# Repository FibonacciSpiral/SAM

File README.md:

# SAM: Single Channel Temperature Monitor  

## Overview

**SAM** (Single-channel Analog Monitor) is a low-cost temperature monitor designed to enable simple temperature monitoring on a variety of TMS heaters. It continuously measures temperature using a Type K thermocouple and alerts operators when the temperature drops below a configured setpoint. The goal is to provide an inexpensive, accurate, and user-friendly thermal monitoring system suitable for industrial or laboratory environments.

## Features
- **Single-channel thermocouple monitoring** via MAX31855K  
- **Configurable setpoint** through a simple 3-button interface (Up, Down, Set)  
- **Real-time temperature display** on a 3-digit seven-segment display  
- **Alert relay output** (N.O. relay circuit) to notify external systems of low-temperature conditions  
- **Modbus TCP/IP server** for remote data retrieval  
- **Web and FTP interfaces** for configuration and resource management  
- **Persistent settings** stored in eMMC non-volatile memory  
- **FreeRTOS-based firmware** using Microchip Studio and ASF (Atmel Software Framework)  

## Hardware Architecture
### Microcontroller
- **MCU Family:** ATSAM4S (ARM Cortex-M4, 120 MHz)  
- **Development Kit:** ATSAM4S Xplained Pro  
- **Networking:** KSZ8851SNL Ethernet controller via SPI  
- **Persistent Storage:** eMMC module (or SD card for prototyping)  

### Sensor Interface
- **Thermocouple Interface Chip:** MAX31855K  
- Provides cold-junction compensation and interfaces with MCU using SPI.

### Display & Input
- **Display:** Three 7-segment LED modules showing real-time temperature or setpoint during configuration.  
- **Buttons:**  
  - **Set:** Enter/exit configuration mode.  
  - **Up/Down:** Adjust setpoint during configuration.  
- **User Feedback:** Flashing display while adjusting setpoint.  

### Relay Output
- **Type:** Normally Open (N.O.) relay  
- **Behavior:**  
  - **High signal:** Normal operation  
  - **Low signal:** Setpoint violation or sensor/power fault  

## Software Architecture
### Operating System
- **RTOS:** FreeRTOS  
- **Language:** C  
- **IDE:** Microchip Studio (Atmel Studio)  

### Modules
#### 1. Temperature Reading
- SPI-based data acquisition from MAX31855K every millisecond for 2 seconds.  
- Average of readings computed for noise reduction.  
- Filtered temperature sent to display, setpoint, and relay tasks.  

#### 2. TCP/IP Stack & Networking
- Based on FreeRTOS+TCP.  
- Includes Ethernet MAC/PHY driver for KSZ8851SNL.  
- Network settings configurable via embedded web server.  

#### 3. Web & FTP Server
- Web interface for IP configuration and device setup.  
- FTP server for uploading web resources (HTML, JS, CSS) stored in eMMC.  

#### 4. Modbus Server
- Implements **Modbus TCP** using the FreeModbus library.  
- Stores current temperature in input register (prototype uses register `1000`).  
- Allows master devices to read temperature remotely.  

#### 5. User Interface Tasks
- **Button Handler:** Interrupt-driven; sends events to state machine task.  
- **Display Driver:** Updates 7-segment display according to operating mode.  
- **Setpoint Task:** Handles setpoint logic, relay control, and NVM storage.  

#### 6. Non-Volatile Memory
- Stores:  
  - Last known setpoint  
  - Network configuration  
  - Web/FTP server resources  
- Implemented with eMMC interface.  

## Development Environment
- **Hardware:** ATSAM4S Xplained Pro + Ethernet1 Xplained Pro extension board  
- **Software:**  
  - Microchip Studio (formerly Atmel Studio)  
  - FreeRTOS  
  - ASF (Atmel Software Framework)  
  - FreeModbus library  

## Prototyping Notes
- SD card may be used as a temporary stand-in for eMMC.  
- Ensure MAX31855K wiring minimizes stray capacitance for accuracy.  
- Software debouncing implemented for all buttons (no hardware debouncing required).  
- Recommended MCU RAM: **≥128kB** (prototype uses 160kB).   

## License
This project is not licensed for redistribution or modification.  
All rights reserved © 2025 Giselle Dockterburke.

## Authors
Software Developed by Giselle Dockterburke at the Hillsboro PC in collaboration with Div Tummala who designed the hardware configuration.

---

**Revision History:**  
See the full svn revision history in the documentation folder.

---

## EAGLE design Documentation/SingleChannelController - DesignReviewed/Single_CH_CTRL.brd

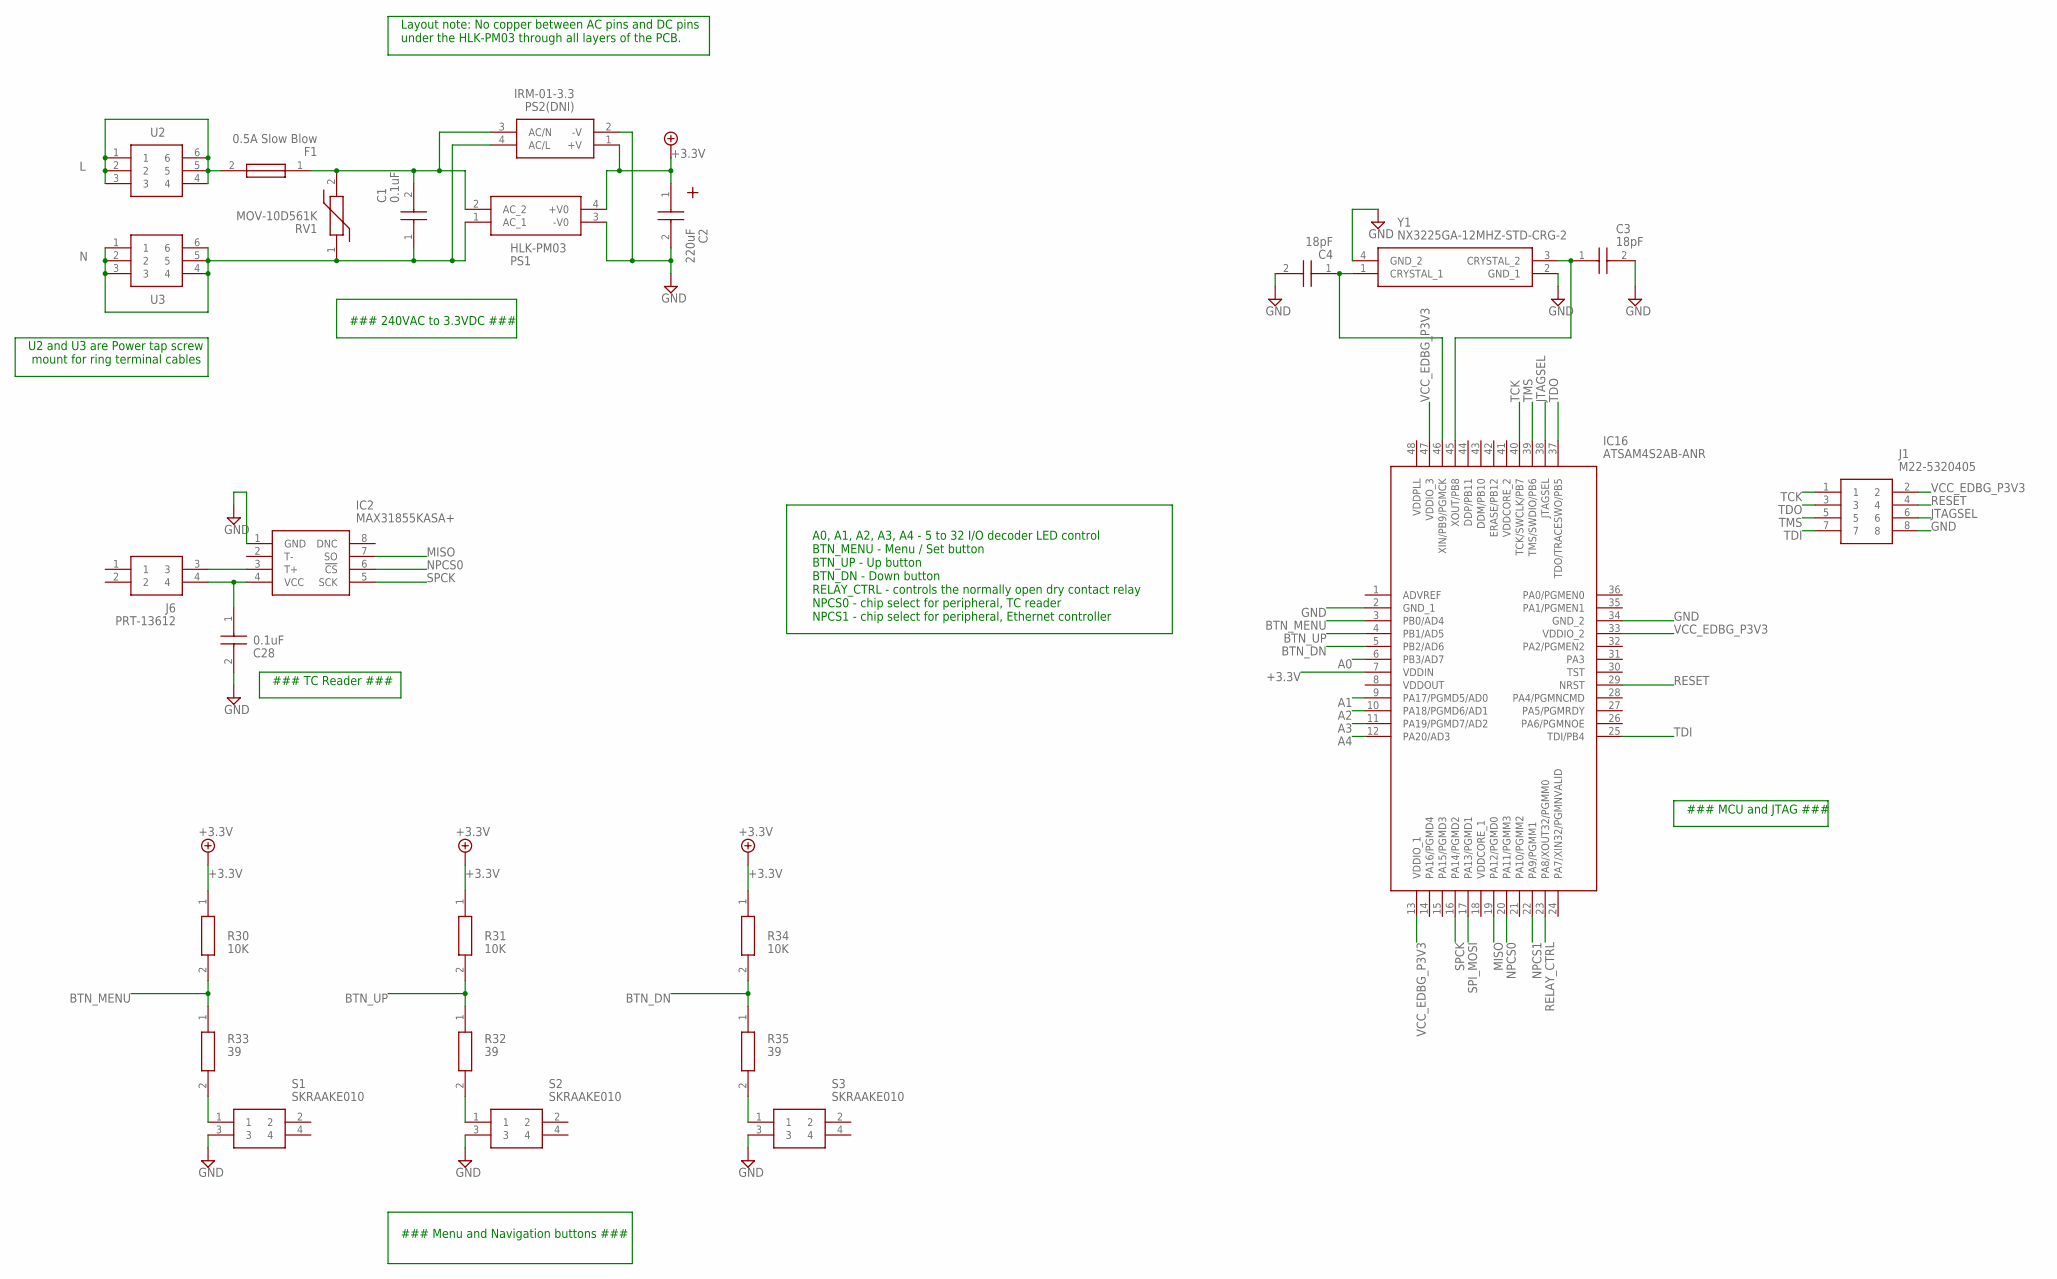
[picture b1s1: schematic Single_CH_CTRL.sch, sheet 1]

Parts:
C1: 0.1uF; B32922X_(18_X_5)
C2: 220uF; CAPPRD250W52D630H1250
C3, C4: 18pF; CAPC1005X56N
C28: 0.1uF; CAPC2012X88N
F1: 0.5A Slow Blow; RST500AMMO
IC2: MAX31855KASA+; SOIC127P600X175-8N
IC16: ATSAM4S2AB-ANR; QFP50P900X900X160-48N
J1: M22-5320405; HUSSP8W50P200_2X4_800X400X500P
J6: PRT-13612; PRT13612
PS1: HLK-PM03; HLKPM03
PS2(DNI): IRM-01-3.3; IRM015
R30, R31, R34: 10K; RESC1005X35N
R32, R33, R35: 39; RESC1005X40N
RV1: MOV-10D561K; MOV10D561K
S1, S2, S3: SKRAAKE010; SKRAAKE010_1
U2, U3: 5055323-9; 50553239
Y1: NX3225GA-12MHZ-STD-CRG-2; NX3225GA12MHZSTDCRG2

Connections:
+3.3V: C2.1 (+), IC16.7 (VDDIN), PS1.4 (+V0), PS2(DNI).1 (+V), R30.1, R31.1, R34.1; also elsewhere on the board
A0: IC16.6 (PB3/AD7)
A1: IC16.9 (PA17/PGMD5/AD0)
A2: IC16.10 (PA18/PGMD6/AD1)
A3: IC16.11 (PA19/PGMD7/AD2)
A4: IC16.12 (PA20/AD3)
BTN_DN: IC16.5 (PB2/AD6), R34.2, R35.1
BTN_MENU: IC16.3 (PB0/AD4), R30.2, R33.1
BTN_UP: IC16.4 (PB1/AD5), R31.2, R32.1
GND: C2.2 (-), C3.2, C4.2, C28.2, IC2.1 (GND), IC16.2 (GND_1), IC16.34 (GND_2), J1.8, PS1.3 (-V0), PS2(DNI).2 (-V), S1.3, S2.3, S3.3, Y1.2 (GND_1), Y1.4 (GND_2); also elsewhere on the board
JTAGSEL: IC16.38 (JTAGSEL), J1.6
L: F1.2, U2.1, U2.2, U2.3, U2.4, U2.5, U2.6
MISO: IC2.7 (SO), IC16.19 (PA12/PGMD0); also elsewhere on the board
N: C1.1, PS1.1 (AC_1), PS2(DNI).4 (AC/L), RV1.1, U3.1, U3.2, U3.3, U3.4, U3.5, U3.6
unnamed: C1.2, F1.1, PS1.2 (AC_2), PS2(DNI).3 (AC/N), RV1.2
unnamed: C3.1, IC16.45 (XOUT/PB8), Y1.3 (CRYSTAL_2)
unnamed: C4.1, IC16.46 (XIN/PB9/PGMCK), Y1.1 (CRYSTAL_1)
unnamed: R33.2, S1.1
unnamed: R32.2, S2.1
unnamed: R35.2, S3.1
unnamed: C28.1, IC2.4 (VCC), J6.4
unnamed: IC2.3 (T+), J6.3
NPCS0: IC2.6 (!CS), IC16.20 (PA11/PGMM3)
NPCS1: IC16.22 (PA9/PGMM1); also elsewhere on the board
RELAY_CTRL: IC16.23 (PA8/XOUT32/PGMM0); also elsewhere on the board
RESET: IC16.29 (NRST), J1.4
SPCK: IC2.5 (SCK), IC16.16 (PA14/PGMD2); also elsewhere on the board
SPI_MOSI: IC16.17 (PA13/PGMD1); also elsewhere on the board
TCK: IC16.40 (TCK/SWCLK/PB7), J1.1
TDI: IC16.25 (TDI/PB4), J1.7
TDO: IC16.37 (TDO/TRACESWO/PB5), J1.3
TMS: IC16.39 (TMS/SWDIO/PB6), J1.5
VCC_EDBG_P3V3: IC16.13 (VDDIO_1), IC16.33 (VDDIO_2), IC16.47 (VDDIO_3), J1.2

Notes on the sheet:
A0, A1, A2, A3, A4 - 5 to 32 I/O decoder LED control BTN_MENU - Menu / Set button BTN_UP - Up button BTN_DN - Down button RELAY_CTRL - controls the normally open dry contact relay NPCS0 - chip select for peripheral, TC reader NPCS1 - chip select for peripheral, Ethernet controller
Layout note: No copper between AC pins and DC pins under the HLK-PM03 through all layers of the PCB.
### 240VAC to 3.3VDC ###
### TC Reader ###
### MCU and JTAG ###
### Menu and Navigation buttons ###
U2 and U3 are Power tap screw mount for ring terminal cables

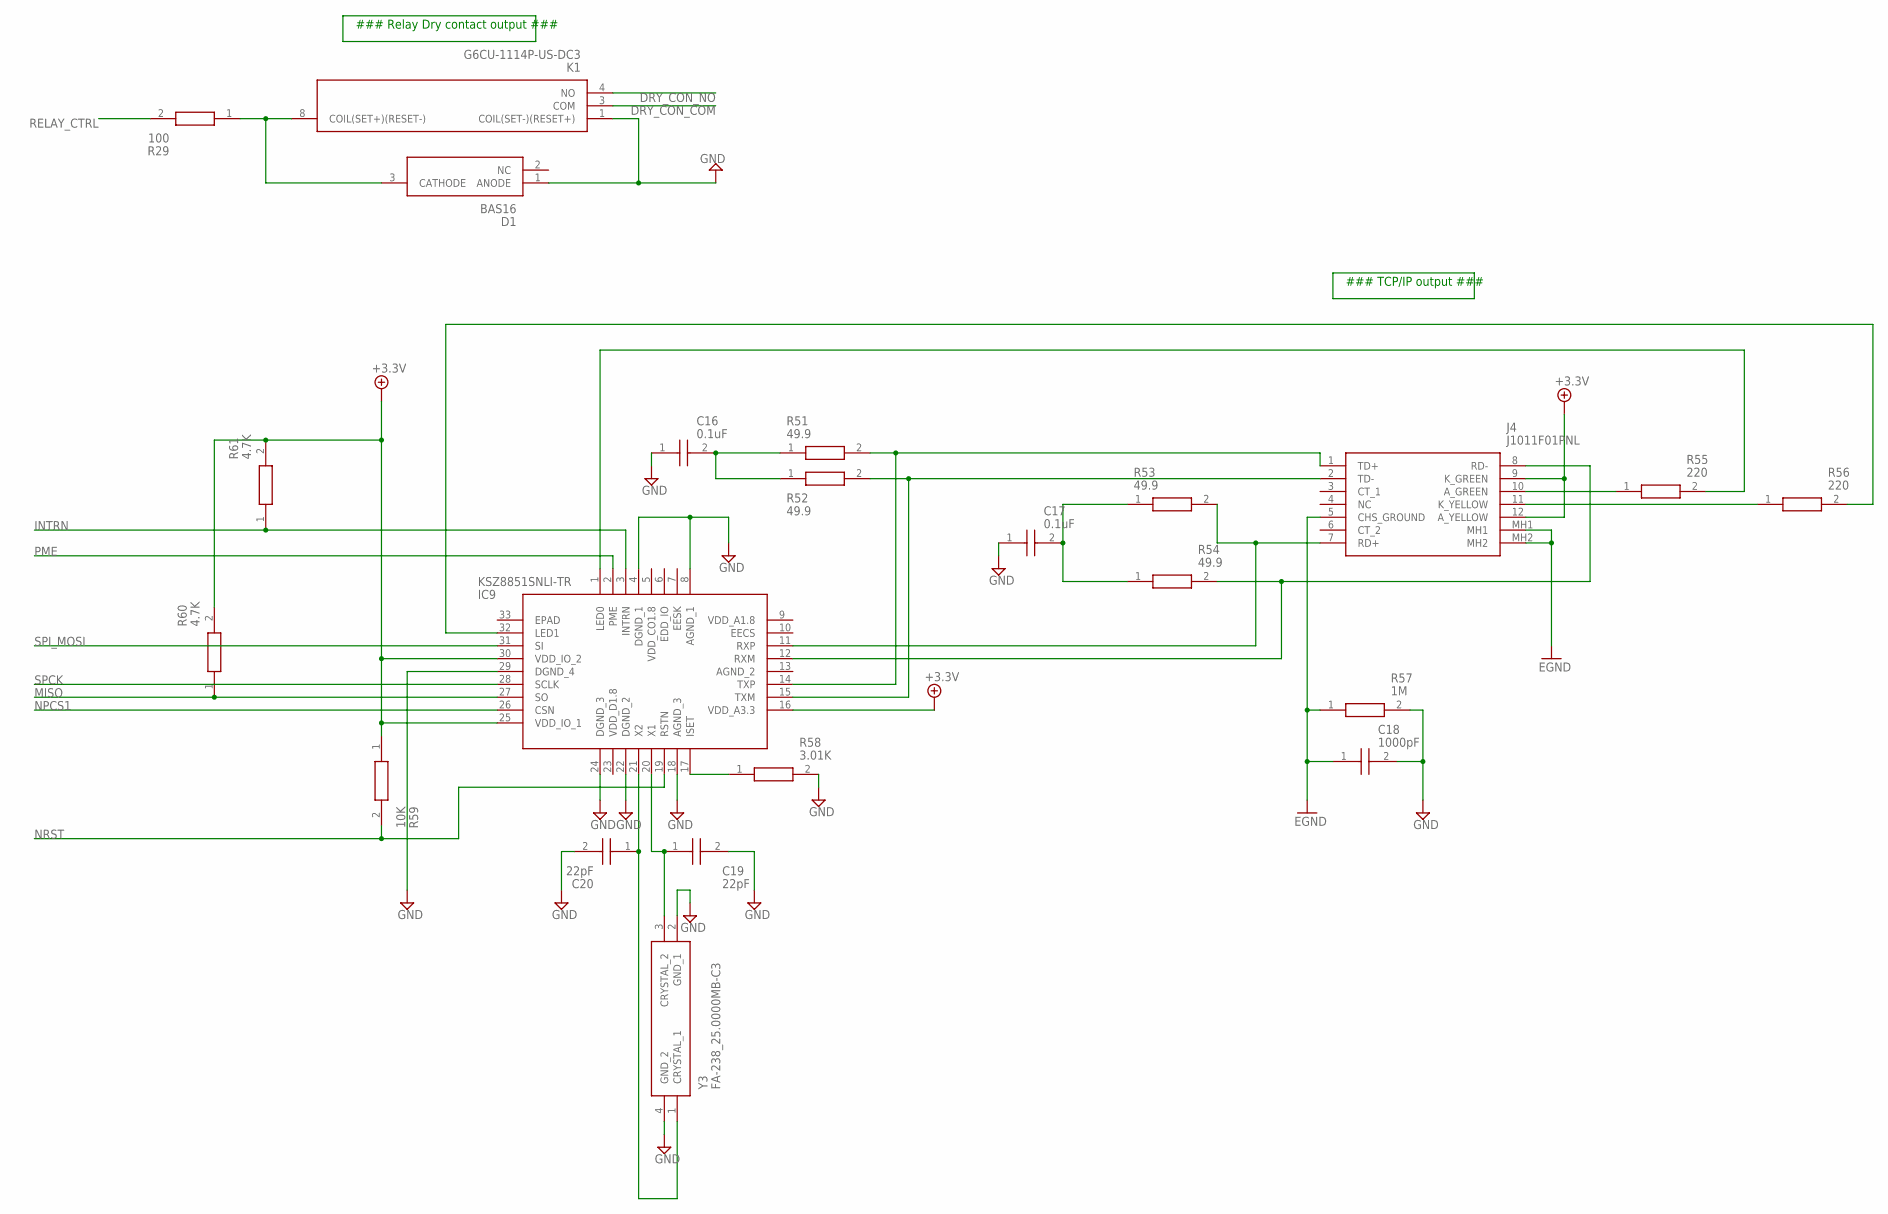
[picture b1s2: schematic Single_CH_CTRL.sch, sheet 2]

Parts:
C16, C17: 0.1uF; C0402
C18: 1000pF; C4520_COMMERCIAL
C19, C20: 22pF; CBR04C
D1: BAS16; SOT95P240X110-3N
IC9: KSZ8851SNLI-TR; QFN50P500X500X100-33N
J4: J1011F01PNL
K1: G6CU-1114P-US-DC3; G6CU1114PUSDC3
R29: 100; ERJP03_PA3_(0603)
R51, R52, R53, R54: 49.9; ERJS02_U02_(0402)
R55, R56: 220; RESC1005X40N
R57: 1M; RESC2012X60N
R58: 3.01K; RESC1005X40N
R59: 10K; RESC1005X40N
R60, R61: 4.7K; RESC1005X40N
Y3: FA-238_25.0000MB-C3; FA238300000MBC0

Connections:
+3.3V: IC9.16 (VDD_A3.3), IC9.25 (VDD_IO_1), IC9.30 (VDD_IO_2), J4.9 (K_GREEN), J4.12 (A_YELLOW), R59.1, R60.2, R61.2; also elsewhere on the board
DRY_CON_COM: K1.3 (COM)
DRY_CON_NO: K1.4 (NO)
GND: C16.1, C17.1, C18.1, C18.2, C19.2, C20.2, D1.1 (ANODE), IC9.4 (DGND_1), IC9.8 (AGND_1), IC9.18 (AGND_3), IC9.22 (DGND_2), IC9.24 (DGND_3), IC9.29 (DGND_4), J4.5 (CHS_GROUND), J4.MH1, J4.MH2, K1.1 (COIL(SET-)(RESET+)), R57.1, R57.2, R58.2, Y3.2 (GND_1), Y3.4 (GND_2); also elsewhere on the board
INTRN: IC9.3 (INTRN), R61.1
MISO: IC9.27 (SO), R60.1; also elsewhere on the board
unnamed: D1.3 (CATHODE), K1.8 (COIL(SET+)(RESET-)), R29.1
unnamed: IC9.14 (TXP), J4.1 (TD+), R51.2
unnamed: IC9.15 (TXM), J4.2 (TD-), R52.2
unnamed: IC9.11 (RXP), J4.7 (RD+), R53.2
unnamed: C16.2, R51.1, R52.1
unnamed: C17.2, R53.1, R54.1
unnamed: IC9.12 (RXM), J4.8 (RD-), R54.2
unnamed: J4.10 (A_GREEN), R55.1
unnamed: J4.11 (K_YELLOW), R56.1
unnamed: IC9.1 (LED0), R55.2
unnamed: IC9.32 (LED1), R56.2
unnamed: C19.1, IC9.20 (X1), Y3.3 (CRYSTAL_2)
unnamed: C20.1, IC9.21 (X2), Y3.1 (CRYSTAL_1)
unnamed: IC9.17 (ISET), R58.1
NPCS1: IC9.26 (CSN); also elsewhere on the board
NRST: IC9.19 (RSTN), R59.2
PME: IC9.2 (PME)
RELAY_CTRL: R29.2; also elsewhere on the board
SPCK: IC9.28 (SCLK); also elsewhere on the board
SPI_MOSI: IC9.31 (SI); also elsewhere on the board

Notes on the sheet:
### Relay Dry contact output ###
### TCP/IP output ###

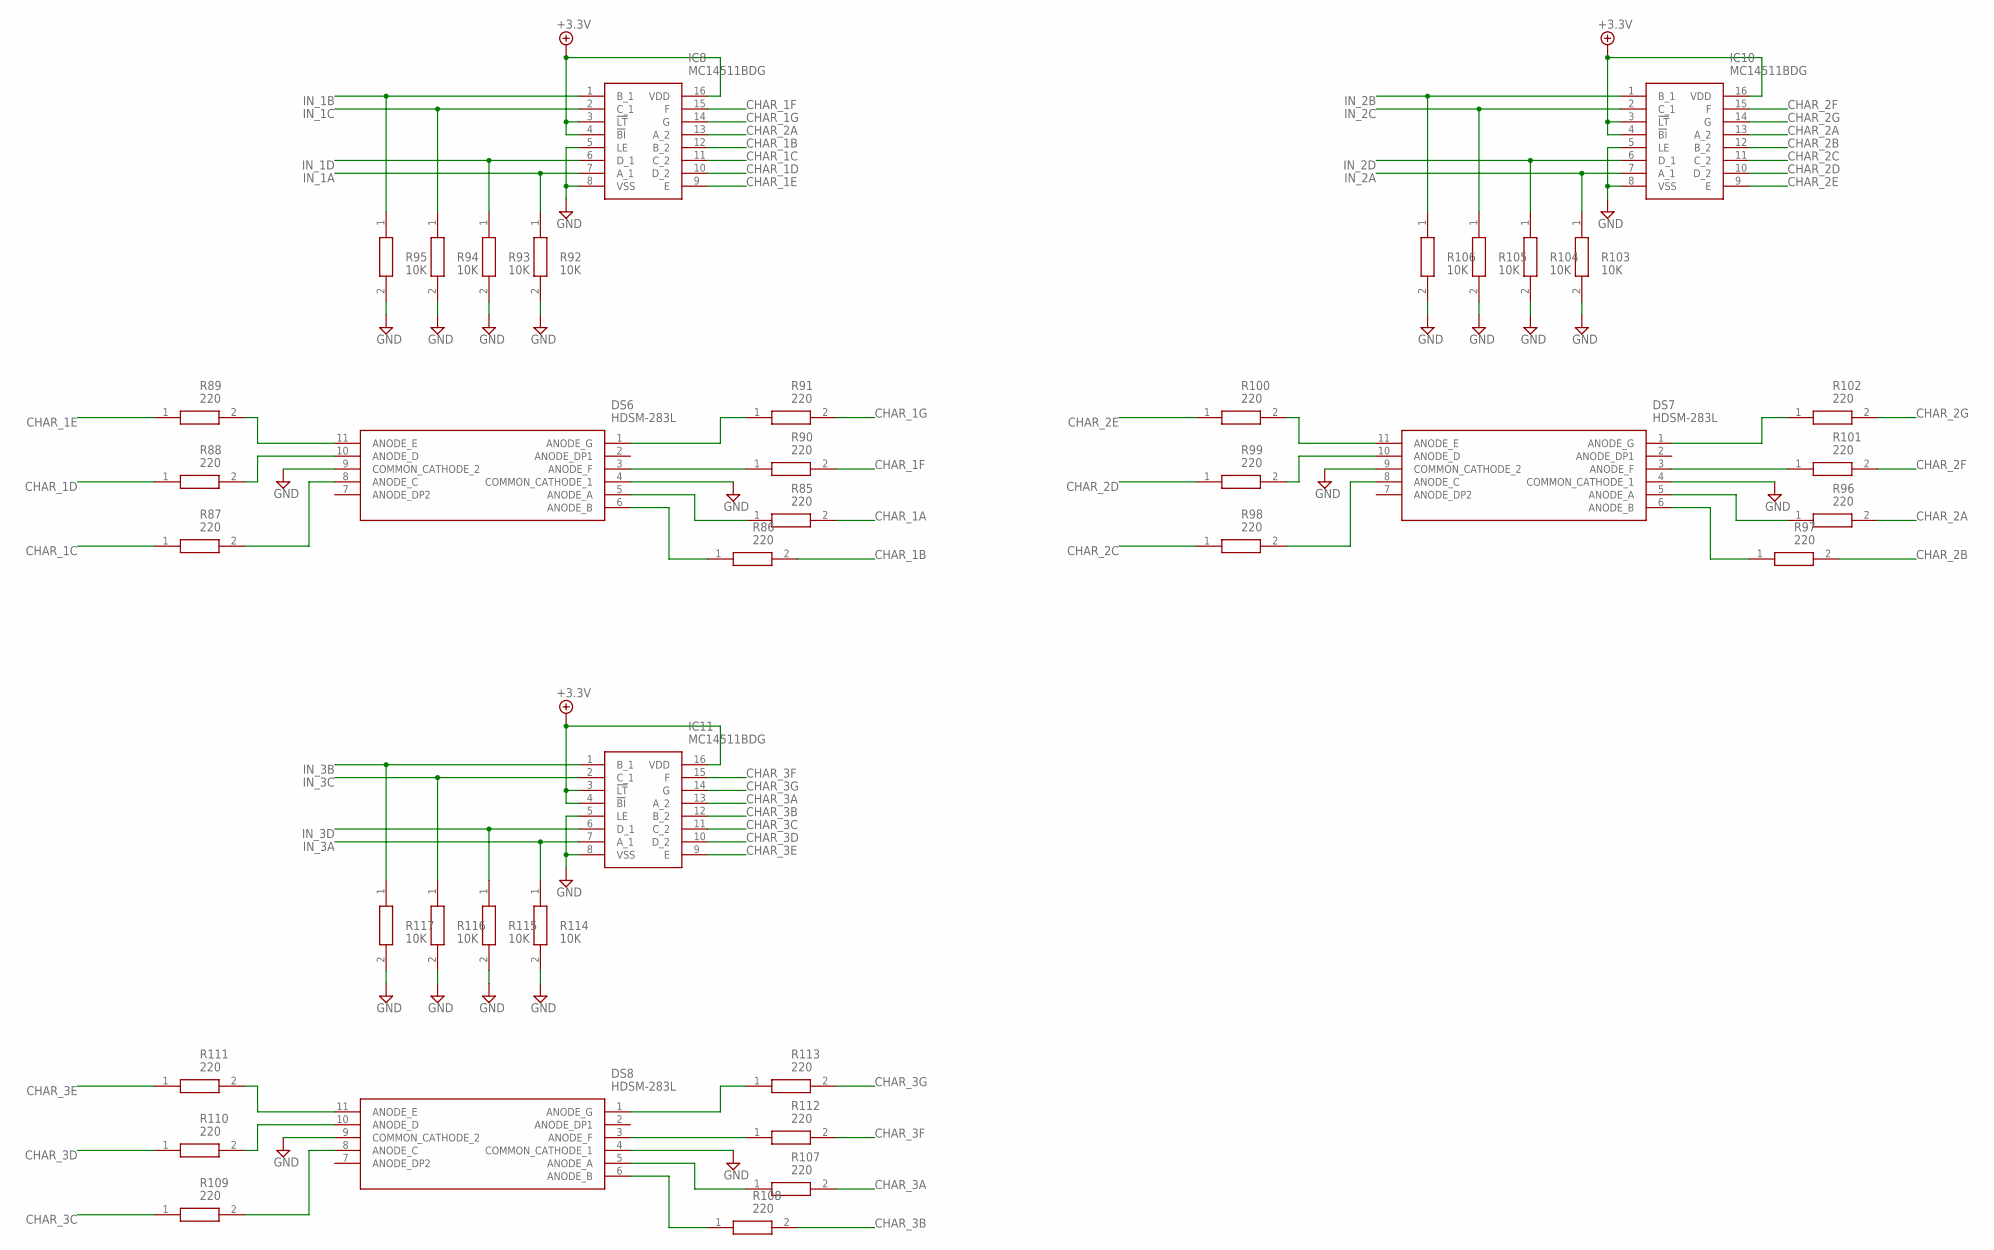
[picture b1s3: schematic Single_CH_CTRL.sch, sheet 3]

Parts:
DS6, DS7, DS8: HDSM-283L; HDSM283L
IC8, IC10, IC11: MC14511BDG; SOIC127P600X175-16N
R85, R86, R87, R88, R89, R90, R91, R96, R97, R98, R99, R100, R101, R102, R107, R108, R109, R110, R111, R112, R113: 220; RESC1005X40N
R92, R93, R94, R95, R103, R104, R105, R106, R114, R115, R116, R117: 10K; RESC1005X35N

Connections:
+5V: IC8.3 (!LT), IC8.4 (!BI), IC8.16 (VDD), IC10.3 (!LT), IC10.4 (!BI), IC10.16 (VDD), IC11.3 (!LT), IC11.4 (!BI), IC11.16 (VDD)
CHAR_1A: R85.2
CHAR_1B: IC8.12 (B_2), R86.2
CHAR_1C: IC8.11 (C_2), R87.1
CHAR_1D: IC8.10 (D_2), R88.1
CHAR_1E: IC8.9 (E), R89.1
CHAR_1F: IC8.15 (F), R90.2
CHAR_1G: IC8.14 (G), R91.2
CHAR_2A: IC8.13 (A_2), IC10.13 (A_2), R96.2
CHAR_2B: IC10.12 (B_2), R97.2
CHAR_2C: IC10.11 (C_2), R98.1
CHAR_2D: IC10.10 (D_2), R99.1
CHAR_2E: IC10.9 (E), R100.1
CHAR_2F: IC10.15 (F), R101.2
CHAR_2G: IC10.14 (G), R102.2
CHAR_3A: IC11.13 (A_2), R107.2
CHAR_3B: IC11.12 (B_2), R108.2
CHAR_3C: IC11.11 (C_2), R109.1
CHAR_3D: IC11.10 (D_2), R110.1
CHAR_3E: IC11.9 (E), R111.1
CHAR_3F: IC11.15 (F), R112.2
CHAR_3G: IC11.14 (G), R113.2
GND: DS6.4 (COMMON_CATHODE_1), DS6.9 (COMMON_CATHODE_2), DS7.4 (COMMON_CATHODE_1), DS7.9 (COMMON_CATHODE_2), DS8.4 (COMMON_CATHODE_1), DS8.9 (COMMON_CATHODE_2), IC8.5 (LE), IC8.8 (VSS), IC10.5 (LE), IC10.8 (VSS), IC11.5 (LE), IC11.8 (VSS), R92.2, R93.2, R94.2, R95.2, R103.2, R104.2, R105.2, R106.2, R114.2, R115.2, R116.2, R117.2; also elsewhere on the board
IN_1A: IC8.7 (A_1), R92.1
IN_1B: IC8.1 (B_1), R95.1
IN_1C: IC8.2 (C_1), R94.1
IN_1D: IC8.6 (D_1), R93.1
IN_2A: IC10.7 (A_1), R103.1
IN_2B: IC10.1 (B_1), R106.1
IN_2C: IC10.2 (C_1), R105.1
IN_2D: IC10.6 (D_1), R104.1
IN_3A: IC11.7 (A_1), R114.1
IN_3B: IC11.1 (B_1), R117.1
IN_3C: IC11.2 (C_1), R116.1
IN_3D: IC11.6 (D_1), R115.1
unnamed: DS6.11 (ANODE_E), R89.2
unnamed: DS6.8 (ANODE_C), R87.2
unnamed: DS6.1 (ANODE_G), R91.1
unnamed: DS6.3 (ANODE_F), R90.1
unnamed: DS6.5 (ANODE_A), R85.1
unnamed: DS6.6 (ANODE_B), R86.1
unnamed: DS6.10 (ANODE_D), R88.2
unnamed: DS7.11 (ANODE_E), R100.2
unnamed: DS7.8 (ANODE_C), R98.2
unnamed: DS7.1 (ANODE_G), R102.1
unnamed: DS7.3 (ANODE_F), R101.1
unnamed: DS7.5 (ANODE_A), R96.1
unnamed: DS7.6 (ANODE_B), R97.1
unnamed: DS7.10 (ANODE_D), R99.2
unnamed: DS8.11 (ANODE_E), R111.2
unnamed: DS8.8 (ANODE_C), R109.2
unnamed: DS8.1 (ANODE_G), R113.1
unnamed: DS8.3 (ANODE_F), R112.1
unnamed: DS8.5 (ANODE_A), R107.1
unnamed: DS8.6 (ANODE_B), R108.1
unnamed: DS8.10 (ANODE_D), R110.2

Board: 4 copper layers, 86 parts (0 on the bottom side), 98 nets, no tracks yet.

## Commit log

2025-11-05 Adding SVN version of project to Git. This is a working protoype of SAM, the super awesome monitor box.
2025-11-05 Adding the logo
2025-11-05 Create README.md with project details
    Added initial README with project overview, features, hardware, and software details.
2025-11-06 Adding design documentation and hardware design.
2025-11-06 Revise README for clarity and detail
    Updated README to enhance project overview, features, and architecture details.
2025-11-06 adding the overview image
2025-11-06 Add images to README for SAM project
2025-11-06 Change overview logo width to 800 pixels
    Updated image width for overview logo in README.
2025-11-06 Add logo to SAM project title in README
    Updated README to include logo in the title section.
2025-11-06 Adding the revision history in for SAM
2025-11-06 Revise README with updated project details
    Updated project description and author credits in README.
2025-11-06 Revise license terms in README.md
    Updated licensing information to restrict redistribution and modification.
